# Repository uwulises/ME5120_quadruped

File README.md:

# ME5120_quadruped
Este proyecto pretende diseñar y fabricar un cuadrúpedo autónomo. La primera etapa corresponde a seleccionar y diseñar el hardware adecuado para montar una estructura funcional.
Las siguientes etapas se centrarán en el control de la caminata y planificación/navegación del entorno.

## TODO
- [x] PCB design
- [x] Basic motor control
- [ ] SPI leg communication
- [ ] UART legs communication
- [ ] MQTT wireless moves callback
- [ ] MuJoCo model update
- [ ] ROS2 model

# Design

# Hardware

## Driver + Rpi Pico Hat
En esta versión se propone utilizar el driver texas drv8302 junto a la [librería SimpleFOC](https://docs.simplefoc.com/drv8302_example)
### SimpleFOC example

### Hat schematic

### Hat Board

## Simulation - Mujoco

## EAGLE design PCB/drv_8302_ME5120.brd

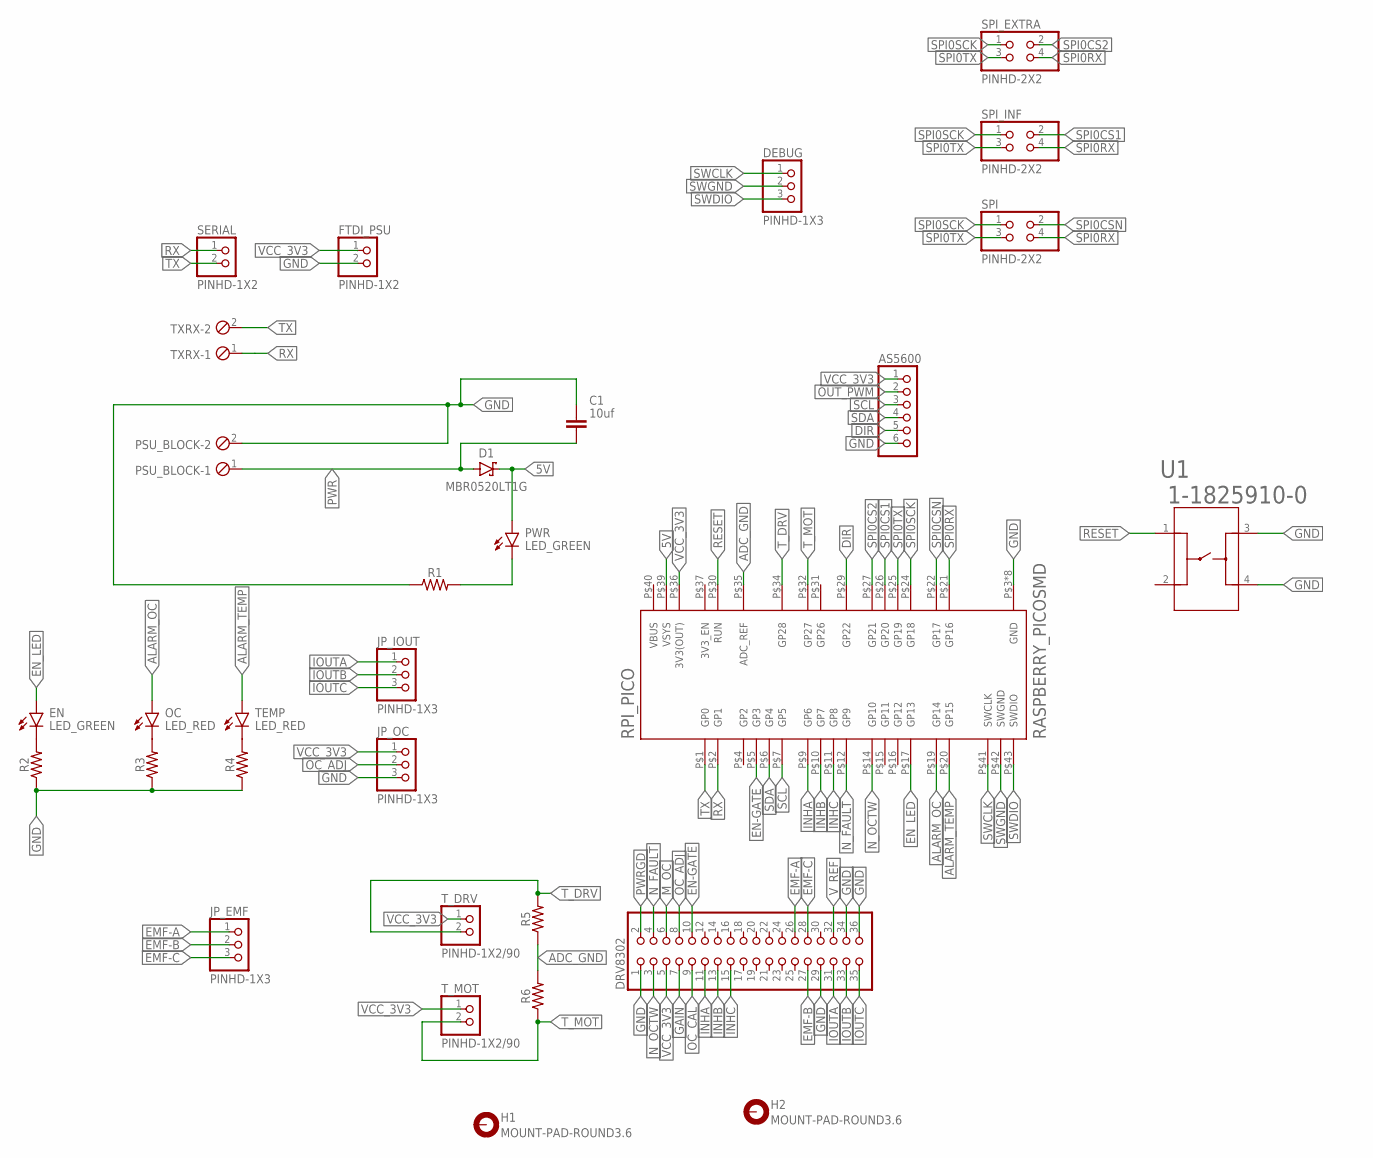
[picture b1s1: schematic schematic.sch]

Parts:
AS5600: PINHD-1X6/90; 1X06/90
C1: 10uf; CAPC2012X110
D1: MBR0520LT1G; SODFL3718X115
DEBUG: PINHD-1X3; 1X03
DRV8302: PINHD-2X18; 2X18
EN: LED_GREEN; LEDC3216X75N_FLAT-G
FTDI_PSU: PINHD-1X2; 1X02
H1, H2: MOUNT-PAD-ROUND3.6; 3,6-PAD
JP_EMF: PINHD-1X3; 1X03
JP_IOUT: PINHD-1X3; 1X03
JP_OC: PINHD-1X3; 1X03
OC: LED_RED; LEDC3216X75N_FLAT-R
PSU_BLOCK: MPT2; 2POL254
PWR: LED_GREEN; LEDC3216X75N_FLAT-G
R1, R2, R3, R4, R5, R6: 0805
RPI_PICO: RASPBERRY_PICOSMD; PICO-PKG-SMD
SERIAL: PINHD-1X2; 1X02
SPI: PINHD-2X2; 2X02
SPI_EXTRA: PINHD-2X2; 2X02
SPI_INF: PINHD-2X2; 2X02
TEMP: LED_RED; LEDC3216X75N_FLAT-R
TXRX: MPT2; 2POL254
T_DRV: PINHD-1X2/90; 1X02/90
T_MOT: PINHD-1X2/90; 1X02/90
U1: 1-1825910-0; SWITCH_1-1825910-0

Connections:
5V: D1.1 (C), PWR.A, RPI_PICO.P$39 (VSYS)
ADC_GND: R5.1, R6.2, RPI_PICO.P$35 (ADC_REF)
ALARM_OC: OC.A, RPI_PICO.P$19 (GP14)
ALARM_TEMP: RPI_PICO.P$20 (GP15), TEMP.A
DIR: AS5600.5, RPI_PICO.P$29 (GP22)
EMF-A: DRV8302.26, JP_EMF.1
EMF-B: DRV8302.27, JP_EMF.2
EMF-C: DRV8302.28, JP_EMF.3
EN-GATE: DRV8302.10, RPI_PICO.P$5 (GP3)
EN_LED: EN.A, RPI_PICO.P$17 (GP13)
GAIN: DRV8302.7
GND: AS5600.6, C1.1, DRV8302.1, DRV8302.29, DRV8302.34, DRV8302.36, FTDI_PSU.2, JP_OC.3, PSU_BLOCK.2, R1.1, R2.1, R3.1, R4.1, RPI_PICO.P$3 (GND), RPI_PICO.P$8 (GND), RPI_PICO.P$13 (GND), RPI_PICO.P$18 (GND), RPI_PICO.P$23 (GND), RPI_PICO.P$28 (GND), RPI_PICO.P$33 (GND), RPI_PICO.P$38 (GND), U1.3, U1.4
INHA: DRV8302.11, RPI_PICO.P$9 (GP6)
INHB: DRV8302.13, RPI_PICO.P$10 (GP7)
INHC: DRV8302.15, RPI_PICO.P$11 (GP8)
IOUTA: DRV8302.31, JP_IOUT.1
IOUTB: DRV8302.33, JP_IOUT.2
IOUTC: DRV8302.35, JP_IOUT.3
M_OC: DRV8302.6
unnamed: PWR.C, R1.2
unnamed: OC.C, R3.2
unnamed: EN.C, R2.2
unnamed: R4.2, TEMP.C
N_FAULT: DRV8302.4, RPI_PICO.P$12 (GP9)
N_OCTW: DRV8302.3, RPI_PICO.P$14 (GP10)
OC_ADJ: DRV8302.8, JP_OC.2
OC_CAL: DRV8302.9
OUT_PWM: AS5600.2
PWR: C1.2, D1.2 (A), PSU_BLOCK.1
PWRGD: DRV8302.2
RESET: RPI_PICO.P$30 (RUN), U1.1
RX: RPI_PICO.P$2 (GP1), SERIAL.1, TXRX.1
SCL: AS5600.3, RPI_PICO.P$7 (GP5)
SDA: AS5600.4, RPI_PICO.P$6 (GP4)
SPI0CS1: RPI_PICO.P$26 (GP20), SPI_INF.2
SPI0CS2: RPI_PICO.P$27 (GP21), SPI_EXTRA.2
SPI0CSN: RPI_PICO.P$22 (GP17), SPI.2
SPI0RX: RPI_PICO.P$21 (GP16), SPI.4, SPI_EXTRA.4, SPI_INF.4
SPI0SCK: RPI_PICO.P$24 (GP18), SPI.1, SPI_EXTRA.1, SPI_INF.1
SPI0TX: RPI_PICO.P$25 (GP19), SPI.3, SPI_EXTRA.3, SPI_INF.3
SWCLK: DEBUG.1, RPI_PICO.P$41 (SWCLK)
SWDIO: DEBUG.3, RPI_PICO.P$43 (SWDIO)
SWGND: DEBUG.2, RPI_PICO.P$42 (SWGND)
TX: RPI_PICO.P$1 (GP0), SERIAL.2, TXRX.2
T_DRV: R5.2, RPI_PICO.P$34 (GP28), T_DRV.2
T_MOT: R6.1, RPI_PICO.P$32 (GP27), T_MOT.2
VBUS: RPI_PICO.P$40 (VBUS)
VCC_3V3: AS5600.1, DRV8302.5, FTDI_PSU.1, JP_OC.1, RPI_PICO.P$36 (3V3(OUT)), T_DRV.1, T_MOT.1
V_REF: DRV8302.32

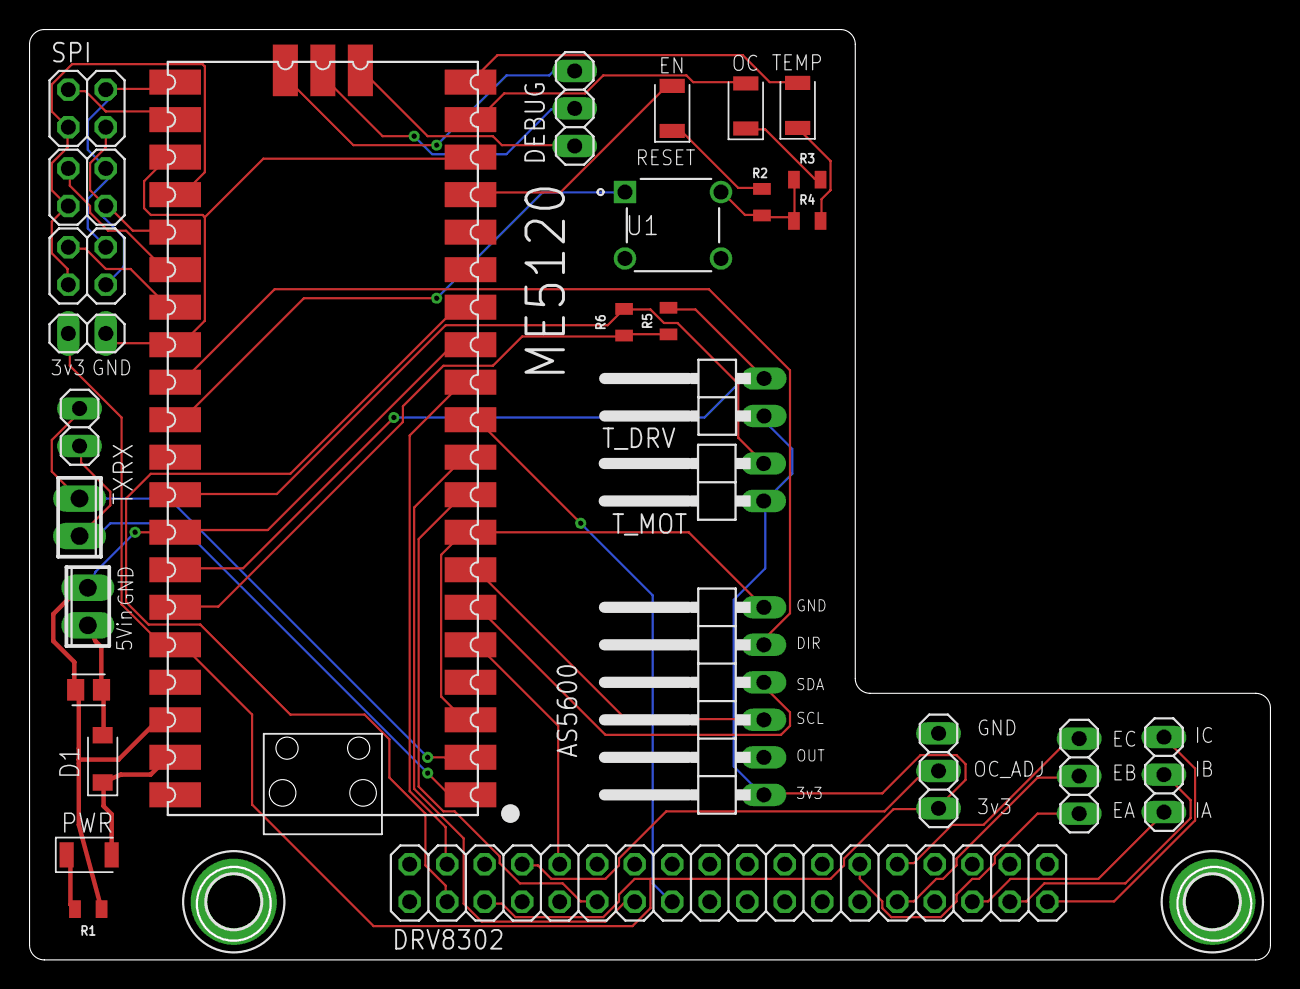
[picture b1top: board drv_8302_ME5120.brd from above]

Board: 2 copper layers, 83.9 x 62.8 mm, 31 parts (0 on the bottom side), 42 nets.

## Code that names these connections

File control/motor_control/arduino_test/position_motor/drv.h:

#ifndef DRV_H
#define DRV_H
#include <SimpleFOC.h>
// DRV8302 pins connections
#include <Arduino.h>
// FOR RASPBERRY PI PICO
#define INH_A 6
#define INH_B 7
#define INH_C 8
#define EN_GATE 3
#define EN_LED 13
#define N_FAULT 9
#define N_OCTW 10
#define ALARM_OC_LED 14
#define TEMP_LED 15
#define DIR 22

void drv_setup(void);
void motor_loop(void);

void motor_move(void);

void update_target(float target);

#endif

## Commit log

2024-04-22 add folders and basic motor definition
2024-04-22 add schematic
2024-04-22 add design checkpoints
2024-04-27 add init align voltage
2024-04-27 update schematic
2024-04-30 update openloop
2024-05-02 add serial event
2024-05-06 add position open loop and serial basic control
2024-05-19 add meshes for simulation
2024-05-20 update meshes with actual model
2024-05-21 update collision
2024-05-23 add foot collision
2024-05-26 add franki texture
2024-07-13 tested with pcb
2024-07-13 separate drv from main ino
2024-07-17 add test for leds
2024-11-12 Pruebas
2024-11-12 otra ve
2025-09-26 add SDK SPI
2025-09-27 add joint control for 3 devices
2025-09-27 update GPIO
2025-09-28 add peripheral device control
2025-09-28 working message to one slave device using 8bit position target
2025-09-28 rm unused files
2025-09-28 add test files for leg control
2025-10-30 add master serial

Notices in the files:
parts and their libraries:
SparkFun-Resistors: Licensing: Creative Commons ShareAlike 4.0 International - https://creativecommons.org/licenses/by-sa/4.0
COPYRIGHT: Copyright (C) 2016 Accelerated Designs. All rights reserved
